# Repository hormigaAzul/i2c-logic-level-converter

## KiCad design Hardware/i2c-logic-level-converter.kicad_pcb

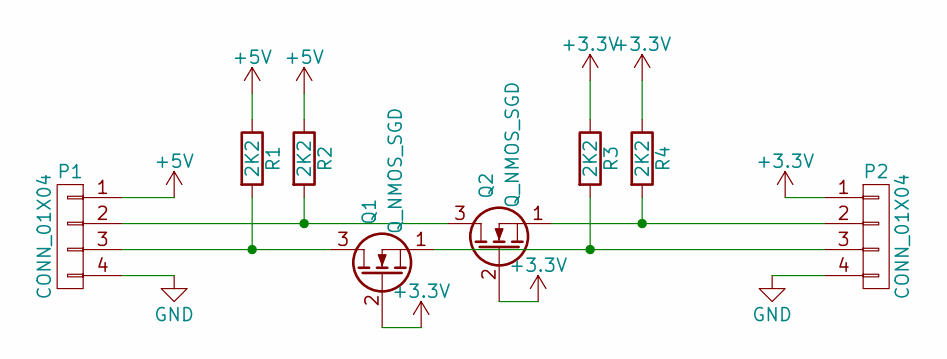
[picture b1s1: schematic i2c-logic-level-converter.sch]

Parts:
P1, P2: CONN_01X04; Pin_Header_Straight_1x04
Q1, Q2: Q_NMOS_SGD; TO-92_Molded_Wide_Oval
R1, R2, R3, R4: 2K2; Resistor_Horizontal_RM10mm

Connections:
+3V3: P2.1, Q1.2 (G), Q2.2 (G), R3.1, R4.1
+5V: P1.1, R1.1, R2.1
GND: P1.4, P2.4
unnamed: P1.2, Q2.3 (D), R2.2
unnamed: P1.3, Q1.3 (D), R1.2
unnamed: P2.2, Q2.1 (S), R4.2
unnamed: P2.3, Q1.1 (S), R3.2

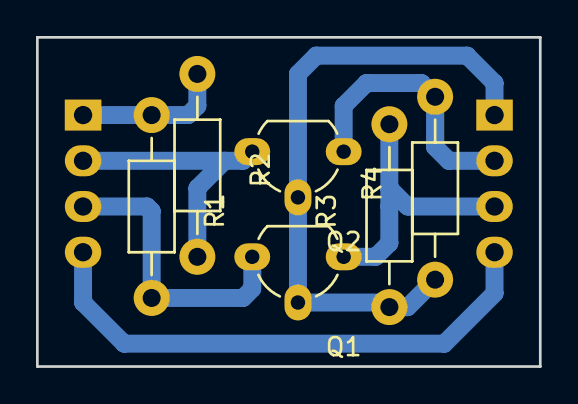
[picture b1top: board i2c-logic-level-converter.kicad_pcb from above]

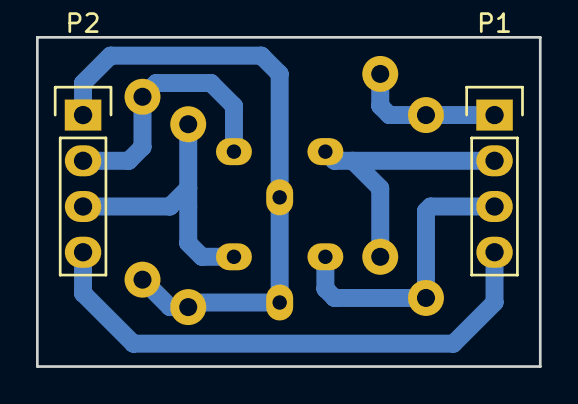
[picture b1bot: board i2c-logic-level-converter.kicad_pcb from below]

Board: 2 copper layers, 27.9 x 18.3 mm, 8 parts (2 on the bottom side), 7 nets.

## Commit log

2016-07-19 Initial setup
2016-07-28 Create files in Kicad
2016-07-28 Improve documenting on schematic
2016-07-28 Correct schematic on documentation
